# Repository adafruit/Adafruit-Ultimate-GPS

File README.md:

## Adafruit Ultimate GPS PCB

<a href="http://www.adafruit.com/products/4279"><br/>
Click here to purchase one from the Adafruit shop</a>
Other versions:
* <a href="https://www.adafruit.com/product/746">Adafruit Ultimate GPS Breakout</a>
* <a href="https://www.adafruit.com/product/3133">Adafruit Ultimate GPS FeatherWing</a>
* <a href="https://www.adafruit.com/product/1272">Adafruit Ultimate GPS Logger Shield</a>
* <a href="https://www.adafruit.com/product/2324">Adafruit Ultimate GPS HAT for Raspberry Pi</a>
* <a href="https://www.adafruit.com/product/1059">Flora Wearable Ultimate GPS Module</a>

PCB files for the Adafruit Ultimate GPS. 

Format is EagleCAD schematic and board layout
* https://www.adafruit.com/product/4279
* https://www.adafruit.com/product/746
* https://www.adafruit.com/product/3133
* https://www.adafruit.com/product/1272
* https://www.adafruit.com/product/2324
* https://www.adafruit.com/product/1059

### Description

These boards are built around the MTK3339 chipset, a no-nonsense, high-quality GPS module that can track up to 22 satellites on 66 channels, has an excellent high-sensitivity receiver (-165 dBm tracking!), and a built-in antenna. It can do up to 10 location updates a second for high speed, high sensitivity logging, or tracking. Power usage is incredibly low, only 20 mA during navigation.

We believe this is the Ultimate GPS module, so we named it that. It's got everything you want and more:

* -165 dBm sensitivity, 10 Hz updates, 66 channels
* 5V friendly design and only 20mA current draw
* RTC battery-compatible
* Built-in datalogging
* PPS output on fix
* Internal patch antenna + u.FL connector for external active antenna
* Fix status LED
* Pulse-Per-Second output

### License

Adafruit invests time and resources providing this open source design, please support Adafruit and open-source hardware by purchasing products from [Adafruit](https://www.adafruit.com)!

Designed by Limor Fried/Ladyada for Adafruit Industries.

Creative Commons Attribution/Share-Alike, all text above must be included in any redistribution. 
See license.txt for additional details.

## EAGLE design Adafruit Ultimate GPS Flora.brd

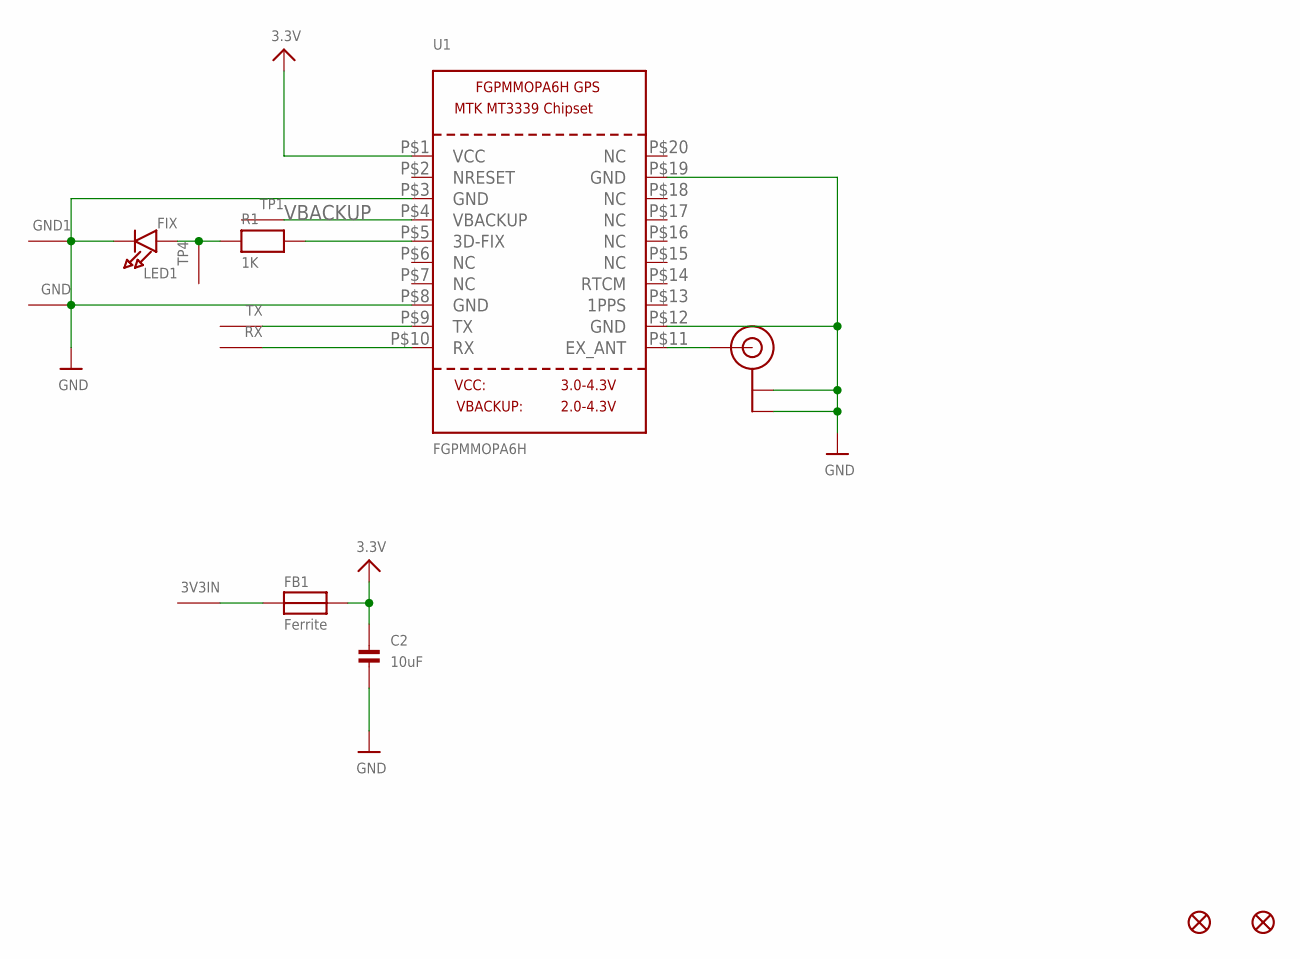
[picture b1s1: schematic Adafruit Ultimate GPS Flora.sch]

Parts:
3V3IN: SEWTAP-2.0IN; SEWINGTAP_2.0
C2: 10uF; 0805
FB1: Ferrite; 0805
FID1, FID2: FIDUCIAL""; FIDUCIAL_1MM
GND, GND1: SEWTAP-2.0IN; SEWINGTAP_2.0
LED1: FIX; CHIPLED_0805
R1: 1K; 0805
RX: SEWTAP-2.0IN; SEWINGTAP_2.0
TP1, TP4: SEWTAP-2.0IN; SEWINGTAP_2.0
TX: SEWTAP-2.0IN; SEWINGTAP_2.0
U1: FGPMMOPA6H
U$20: U.FL

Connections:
3.3V: C2.1, FB1.2, U1.P$1 (VCC)
GND: C2.2, GND.P$1, GND1.P$1, LED1.C, U1.P$3 (GND), U1.P$8 (GND), U1.P$12 (GND), U1.P$19 (GND), U$20.P$1 (GND), U$20.P$2 (GND)
unnamed: LED1.A, R1.1, TP4.P$1
unnamed: R1.2, U1.P$5 (3D-FIX)
unnamed: 3V3IN.P$1, FB1.1
unnamed: U1.P$11 (EX_ANT), U$20.P$3 (SIGNAL)
RX: RX.P$1, U1.P$10 (RX)
TX: TX.P$1, U1.P$9 (TX)
VBACKUP: TP1.P$1, U1.P$4 (VBACKUP)

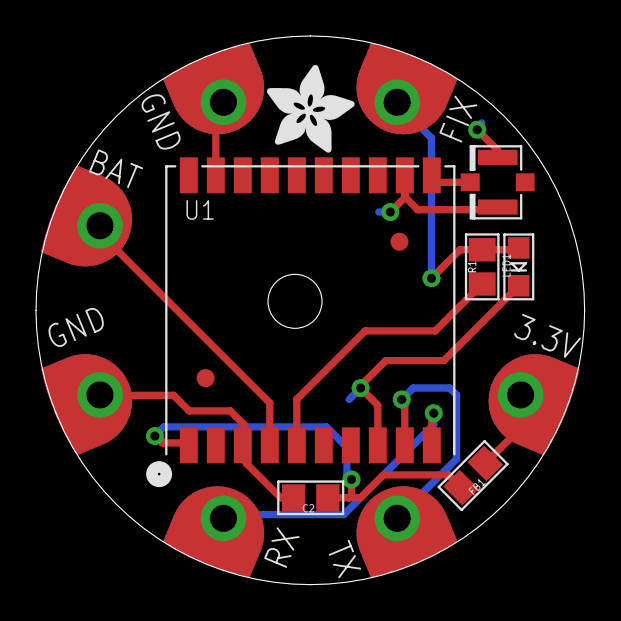
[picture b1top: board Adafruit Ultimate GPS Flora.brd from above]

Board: 2 copper layers, 30.5 x 30.5 mm, 17 parts (1 on the bottom side), 9 nets.

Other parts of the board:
U$6: ADAFRUIT_5MM
U$7: FLORASMALL

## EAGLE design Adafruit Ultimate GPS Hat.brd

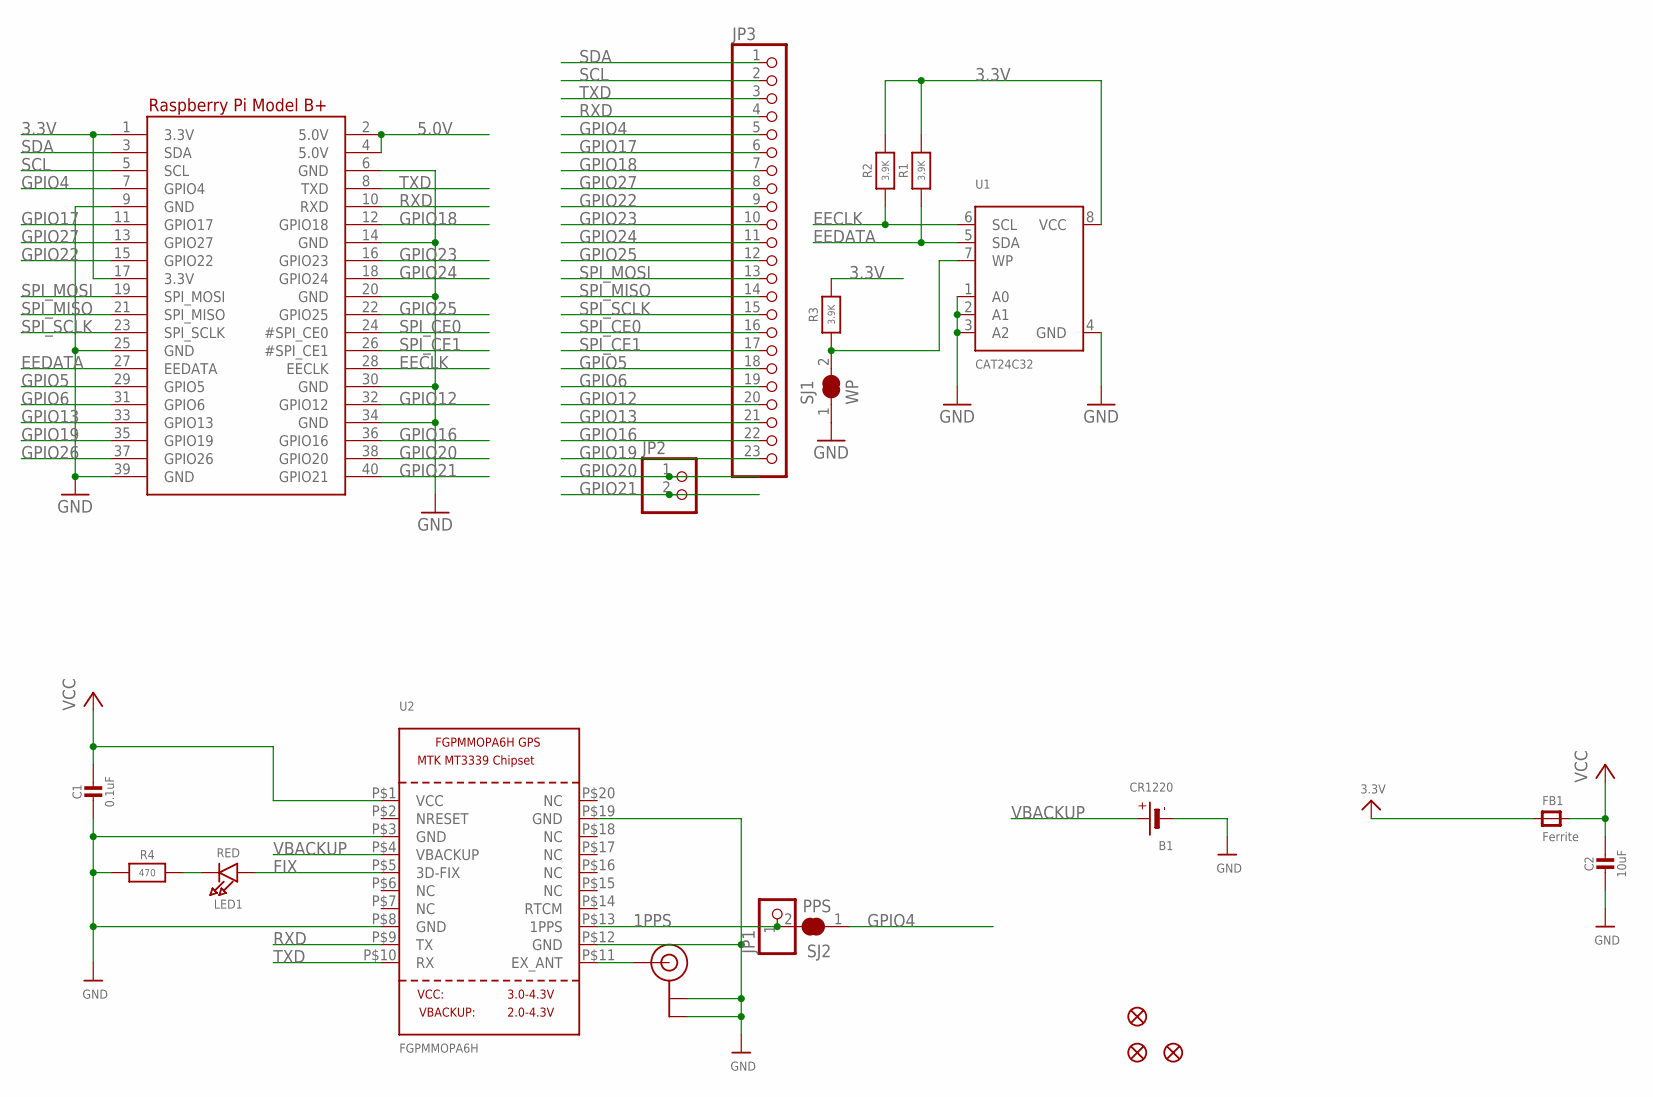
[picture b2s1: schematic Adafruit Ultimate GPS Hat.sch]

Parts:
B1: CR1220
C1: 0.1uF; 0805-NO
C2: 10uF; 0805-NO
FB1: Ferrite; 0805
FID1, FID2, FID3: FIDUCIAL_1MM
JP1: PINHD-1X1CB; 1X01-CLEANBIG
JP2: HEADER-1X2ROUND; 1X02_ROUND
JP3: HEADER-1X23; 1X23_ROUND_70MIL
LED1: RED; CHIPLED_0805
R1, R2, R3: 3.9K; 0805-NO
R4: 470; 0805-NO
RPI1: RASPBERRYPI_BPLUS_HATSLOTS; PI_HAT_SLOTS
SJ1: WP; SOLDERJUMPER_CLOSEDWIRE
SJ2: PPS; SOLDERJUMPER_CLOSEDWIRE
U1: CAT24C32; SOIC8_150MIL
U2: FGPMMOPA6H
U$20: U.FL

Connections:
1PPS: JP1.1, SJ2.2, U2.P$13 (1PPS)
3.3V: FB1.1, R1.2, R2.2, R3.2, RPI1.1 (3.3V), RPI1.17 (3.3V), U1.8 (VCC)
5.0V: RPI1.2 (5.0V), RPI1.4 (5.0V)
EECLK: R2.1, RPI1.28 (EECLK), U1.6 (SCL)
EEDATA: R1.1, RPI1.27 (EEDATA), U1.5 (SDA)
FIX: LED1.A, U2.P$5 (3D-FIX)
GND: B1.-, C1.2, C2.2, R4.1, RPI1.6 (GND), RPI1.9 (GND), RPI1.14 (GND), RPI1.20 (GND), RPI1.25 (GND), RPI1.30 (GND), RPI1.34 (GND), RPI1.39 (GND), SJ1.1, U1.1 (A0), U1.2 (A1), U1.3 (A2), U1.4 (GND), U2.P$3 (GND), U2.P$8 (GND), U2.P$12 (GND), U2.P$19 (GND), U$20.P$1 (GND), U$20.P$2 (GND)
GPIO4: JP3.5, RPI1.7 (GPIO4), SJ2.1
GPIO5: JP3.18, RPI1.29 (GPIO5)
GPIO6: JP3.19, RPI1.31 (GPIO6)
GPIO12: JP3.20, RPI1.32 (GPIO12)
GPIO13: JP3.21, RPI1.33 (GPIO13)
GPIO16: JP3.22, RPI1.36 (GPIO16)
GPIO17: JP3.6, RPI1.11 (GPIO17)
GPIO18: JP3.7, RPI1.12 (GPIO18)
GPIO19: JP3.23, RPI1.35 (GPIO19)
GPIO20: JP2.1, RPI1.38 (GPIO20)
GPIO21: JP2.2, RPI1.40 (GPIO21)
GPIO22: JP3.9, RPI1.15 (GPIO22)
GPIO23: JP3.10, RPI1.16 (GPIO23)
GPIO24: JP3.11, RPI1.18 (GPIO24)
GPIO25: JP3.12, RPI1.22 (GPIO25)
GPIO26: RPI1.37 (GPIO26)
GPIO27: JP3.8, RPI1.13 (GPIO27)
unnamed: R3.1, SJ1.2, U1.7 (WP)
unnamed: LED1.C, R4.2
unnamed: U2.P$11 (EX_ANT), U$20.P$3 (SIGNAL)
RXD: JP3.4, RPI1.10 (RXD), U2.P$9 (TX)
SCL: JP3.2, RPI1.5 (SCL)
SDA: JP3.1, RPI1.3 (SDA)
SPI_CE0: JP3.16, RPI1.24 (#SPI_CE0)
SPI_CE1: JP3.17, RPI1.26 (#SPI_CE1)
SPI_MISO: JP3.14, RPI1.21 (SPI_MISO)
SPI_MOSI: JP3.13, RPI1.19 (SPI_MOSI)
SPI_SCLK: JP3.15, RPI1.23 (SPI_SCLK)
TXD: JP3.3, RPI1.8 (TXD), U2.P$10 (RX)
VBACKUP: B1.+$1 (+), B1.+$2 (+), U2.P$4 (VBACKUP)
VCC: C1.1, C2.1, FB1.2, U2.P$1 (VCC)

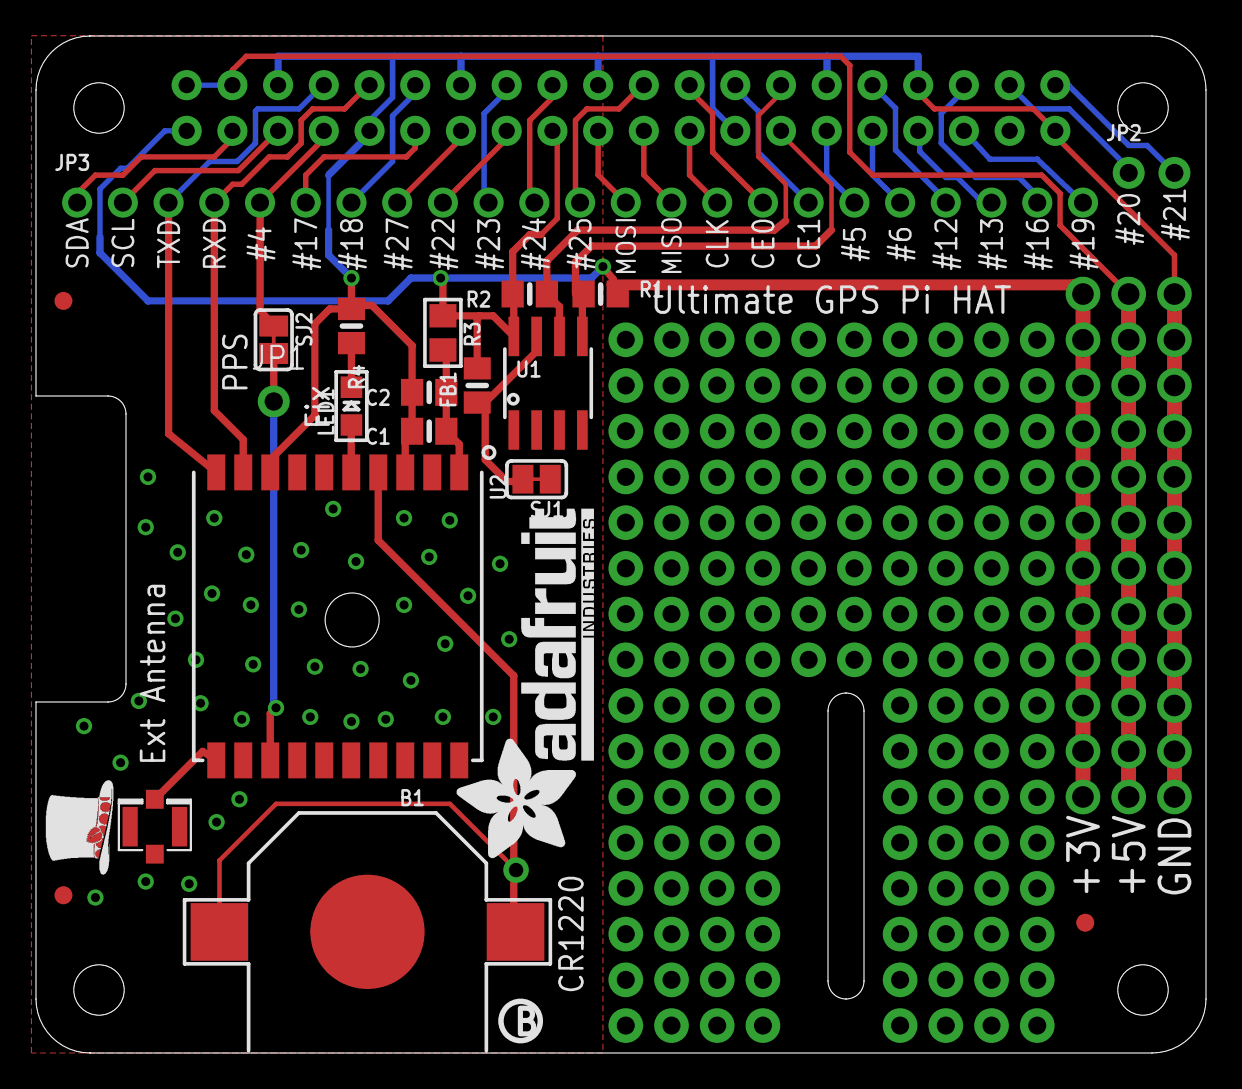
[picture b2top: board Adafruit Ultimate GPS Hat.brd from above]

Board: 2 copper layers, 65.0 x 56.5 mm, 24 parts (0 on the bottom side), 37 nets.

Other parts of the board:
U$3: ADAFRUIT_TEXT_20MM
U$4: PIHATLOGO
U$6: PCBFEAT-REV-056

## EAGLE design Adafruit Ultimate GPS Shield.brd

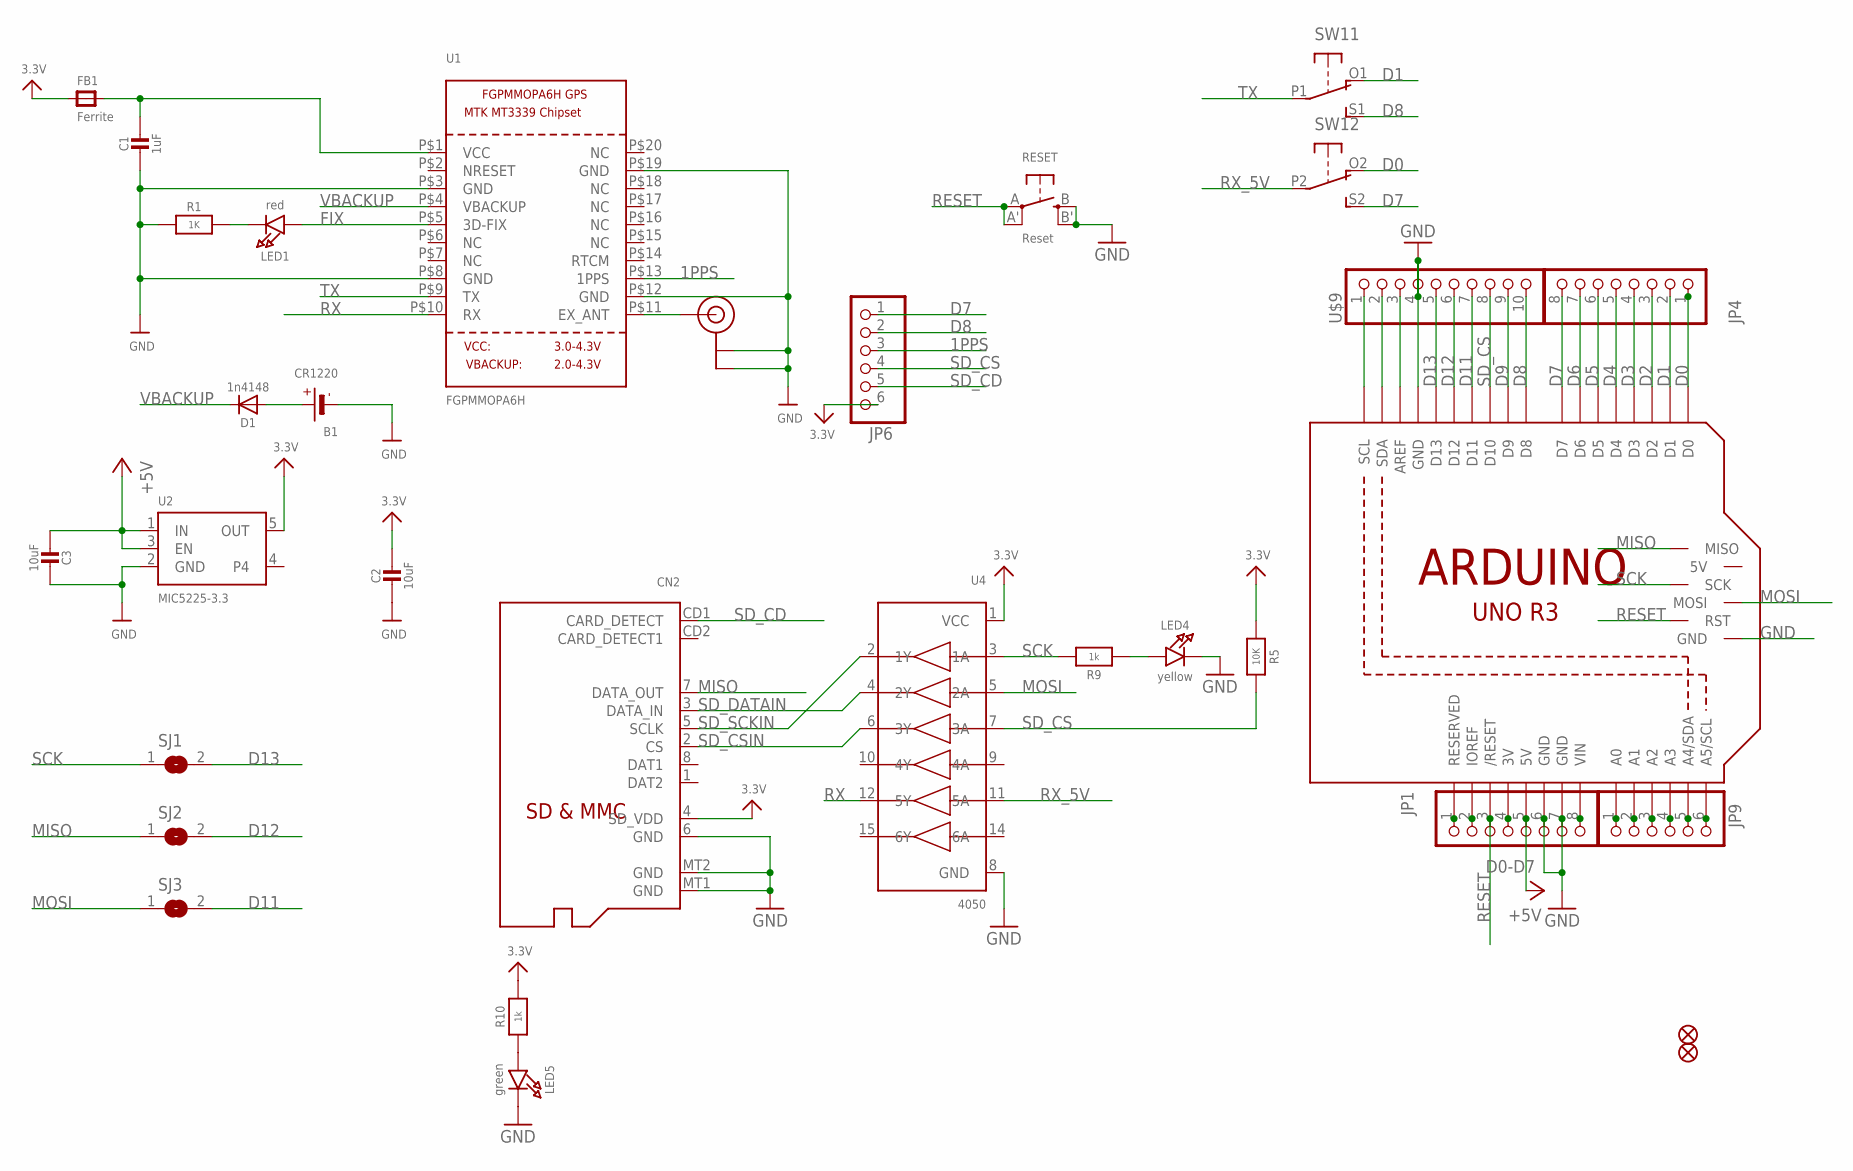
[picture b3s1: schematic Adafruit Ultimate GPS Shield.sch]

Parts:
B1: CR1220
C1: 1uF; 0805-NO
C2, C3: 10uF; 0805-NO
CN2: MICROSD
D1: 1n4148; SOD-323
FB1: Ferrite; 0805
FID1, FID2: FIDUCIAL""; FIDUCIAL_1MM
JP1: D0-D7; 1X08-BIG
JP4: PINHD-1X8BIG; 1X08-BIG
JP6, JP9: PINHD-1X6B; 1X06-BIG
LED1: red; CHIPLED_0805_NOOUTLINE
LED4: yellow; CHIPLED_0805_NOOUTLINE
LED5: green; CHIPLED_0805_NOOUTLINE
M1: ARDUINO_R3_ICSP_NODIM; ARDUINOR3_ICSP_NODIM
R1: 1K; 0805-NO
R5: 10K; 0805-NO
R9, R10: 1k; 0805-NO
RESET: Reset; EVQ-Q2
SJ1, SJ2, SJ3: SOLDERJUMPER; SOLDERJUMPER_ARROW_NOPASTE
SW1: DPDT-EG1390; EG1390
U1: FGPMMOPA6H
U2: MIC5225-3.3; SOT23-5
U4: 4050; SOIC16
U$9: PINHD-1X10; 1X10-BIG
U$20: U.FL

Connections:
1PPS: JP6.3, U1.P$13 (1PPS)
3.3V: C2.1, CN2.4 (SD_VDD), FB1.1, JP6.6, R5.1, R10.2, U2.5 (OUT), U4.1 (VCC)
3V: JP1.4, M1.3V
+5V: C3.1, JP1.5, M1.5V, U2.1 (IN), U2.3 (EN)
A0: JP9.1, M1.A0
A1: JP9.2, M1.A1
A2: JP9.3, M1.A2
A3: JP9.4, M1.A3
A4: JP9.5, M1.A4 (A4/SDA)
A5: JP9.6, M1.A5 (A5/SCL)
AREF: M1.AREF, U$9.3
D0: JP4.1, M1.D0, SW1.O2 (O)
D1: JP4.2, M1.D1, SW1.O1 (O)
D2: JP4.3, M1.D2
D3: JP4.4, M1.D3
D4: JP4.5, M1.D4
D5: JP4.6, M1.D5
D6: JP4.7, M1.D6
D7: JP4.8, JP6.1, M1.D7, SW1.S2 (S)
D8: JP6.2, M1.D8, SW1.S1 (S), U$9.10
D9: M1.D9, U$9.9
D11: M1.D11, SJ3.2, U$9.7
D12: M1.D12, SJ2.2, U$9.6
D13: M1.D13, SJ1.2, U$9.5
FIX: LED1.A, U1.P$5 (3D-FIX)
GND: B1.-, C1.2, C2.2, C3.2, CN2.6 (GND), CN2.MT1 (GND), CN2.MT2 (GND), JP1.6, JP1.7, LED4.C, LED5.C, M1.GND, M1.GND@1 (GND), M1.GND@2 (GND), M1.GND@3 (GND), R1.1, RESET.B (S), RESET.B' (S1), U1.P$3 (GND), U1.P$8 (GND), U1.P$12 (GND), U1.P$19 (GND), U2.2 (GND), U4.8 (GND), U$9.4, U$20.P$1 (GND), U$20.P$2 (GND)
IOREF: JP1.2, M1.IOREF
MISO: CN2.7 (DATA_OUT), M1.MISO, SJ2.1
MOSI: M1.MOSI, SJ3.1, U4.5 (2A)
unnamed: C1.1, FB1.2, U1.P$1 (VCC)
unnamed: LED1.C, R1.2
unnamed: B1.+$1 (+), B1.+$2 (+), D1.A
unnamed: U1.P$11 (EX_ANT), U$20.P$3 (SIGNAL)
unnamed: LED4.A, R9.1
unnamed: LED5.A, R10.1
NC: JP1.1, M1.RESERVED
RESET: JP1.3, M1.RESET (/RESET), M1.RESET_ICSP (RST), RESET.A, RESET.A' (P1)
RX: U1.P$10 (RX), U4.12 (5Y)
RX_5V: SW1.P2, U4.11 (5A)
SCK: M1.SCK, R9.2, SJ1.1, U4.3 (1A)
SCL: M1.SCL, U$9.1
SDA: M1.SDA, U$9.2
SD_CD: CN2.CD1 (CARD_DETECT), JP6.5
SD_CS: JP6.4, M1.D10, R5.2, U4.7 (3A), U$9.8
SD_CSIN: CN2.2 (CS), U4.6 (3Y)
SD_DATAIN: CN2.3 (DATA_IN), U4.4 (2Y)
SD_SCKIN: CN2.5 (SCLK), U4.2 (1Y)
TX: SW1.P1, U1.P$9 (TX)
VBACKUP: D1.C, U1.P$4 (VBACKUP)
VIN: JP1.8, M1.VIN

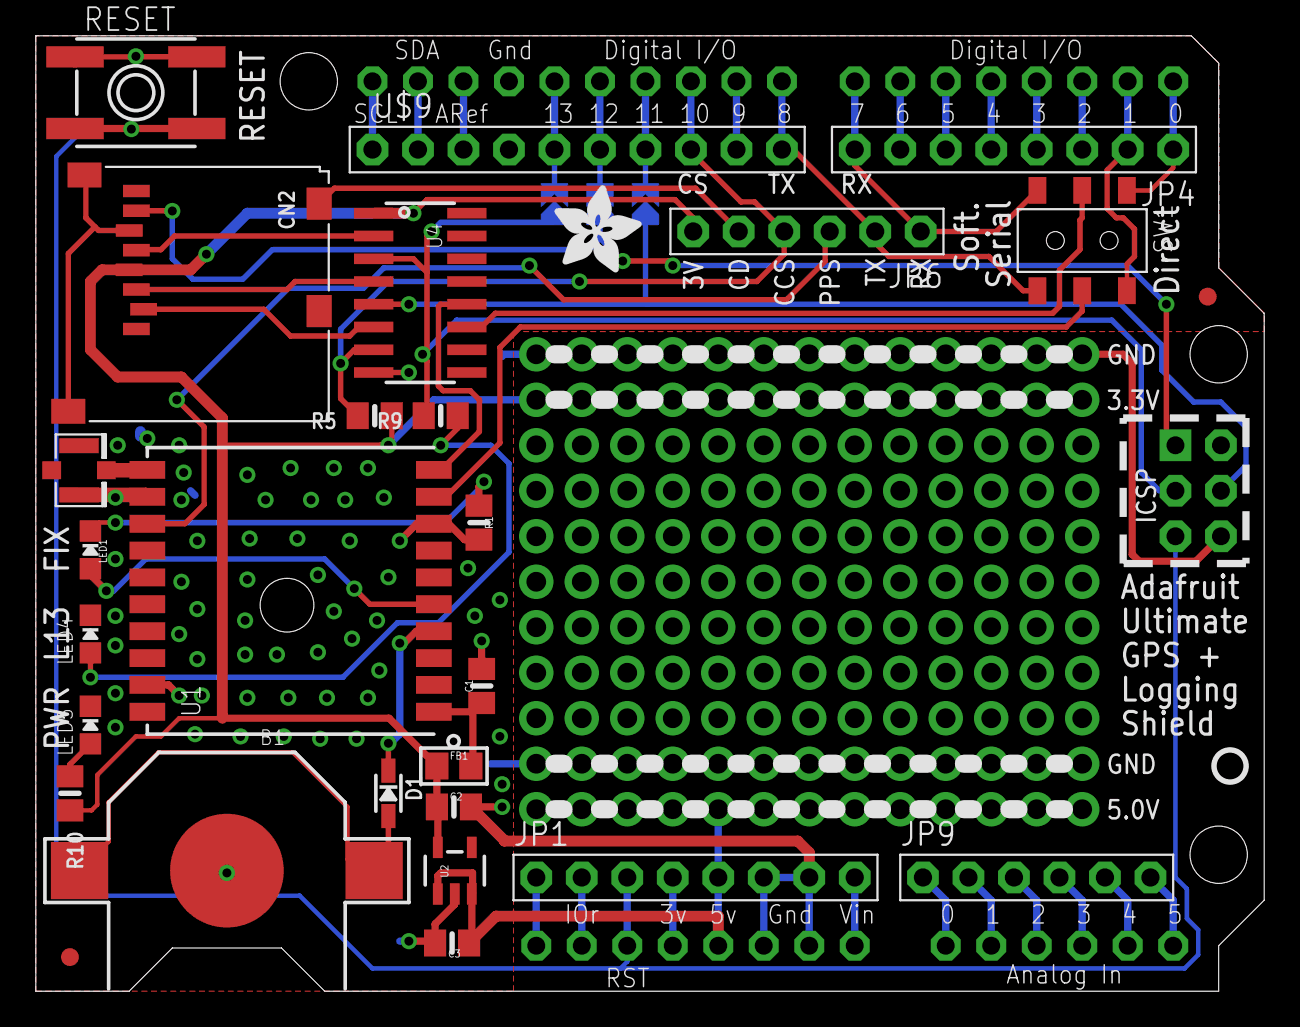
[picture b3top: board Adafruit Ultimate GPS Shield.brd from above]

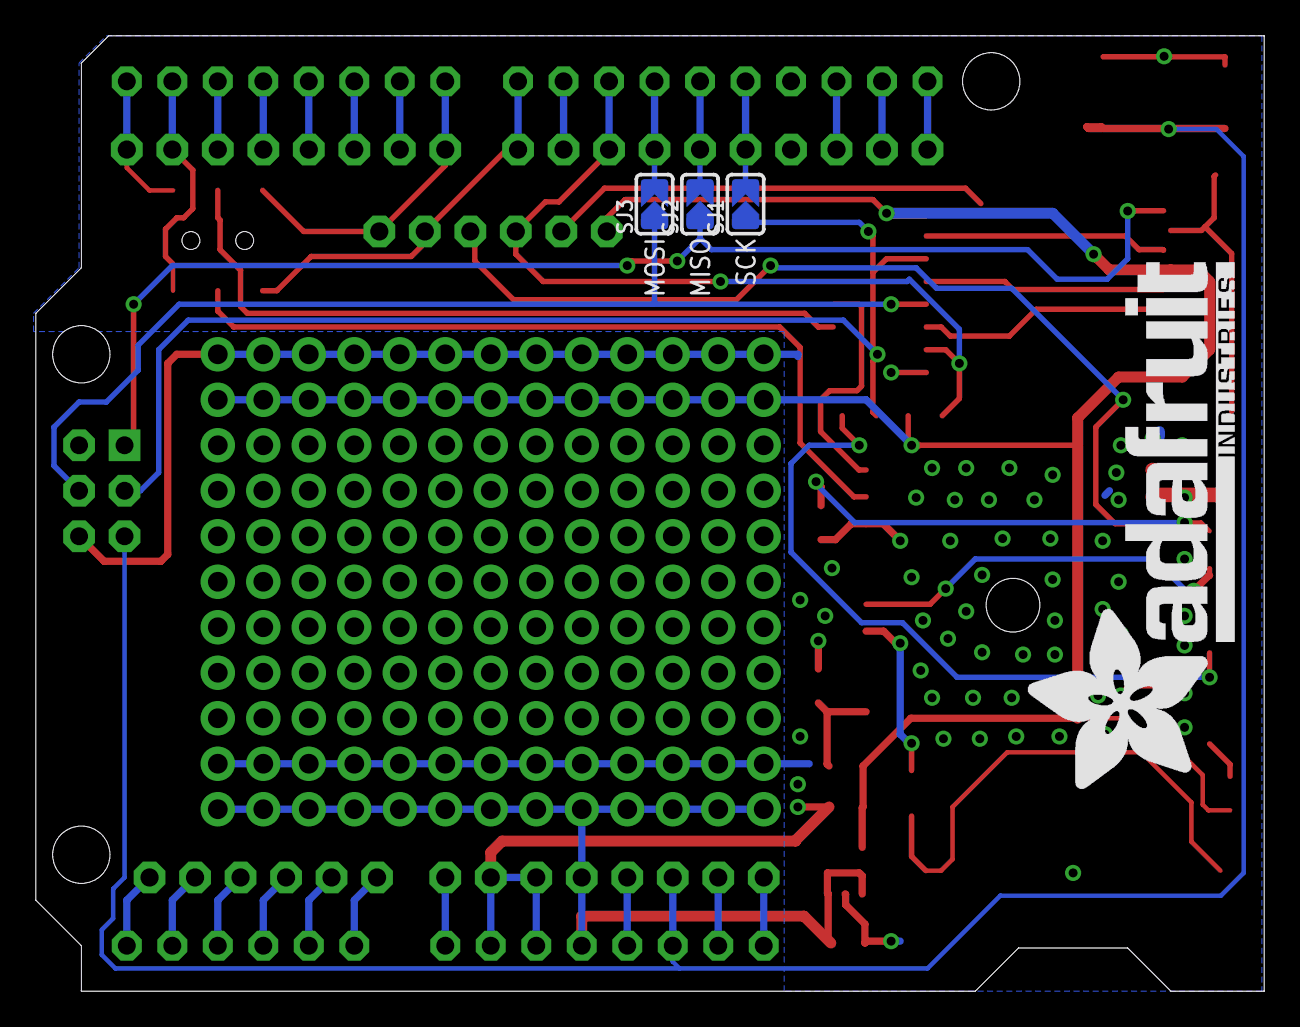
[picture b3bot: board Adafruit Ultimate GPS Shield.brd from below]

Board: 2 copper layers, 68.6 x 53.3 mm, 34 parts (4 on the bottom side), 50 nets.

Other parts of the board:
U$13: ADAFRUIT_5MM
U$15: ADAFRUIT_TEXT_30MM
U$16: PCBFEAT-REV-040

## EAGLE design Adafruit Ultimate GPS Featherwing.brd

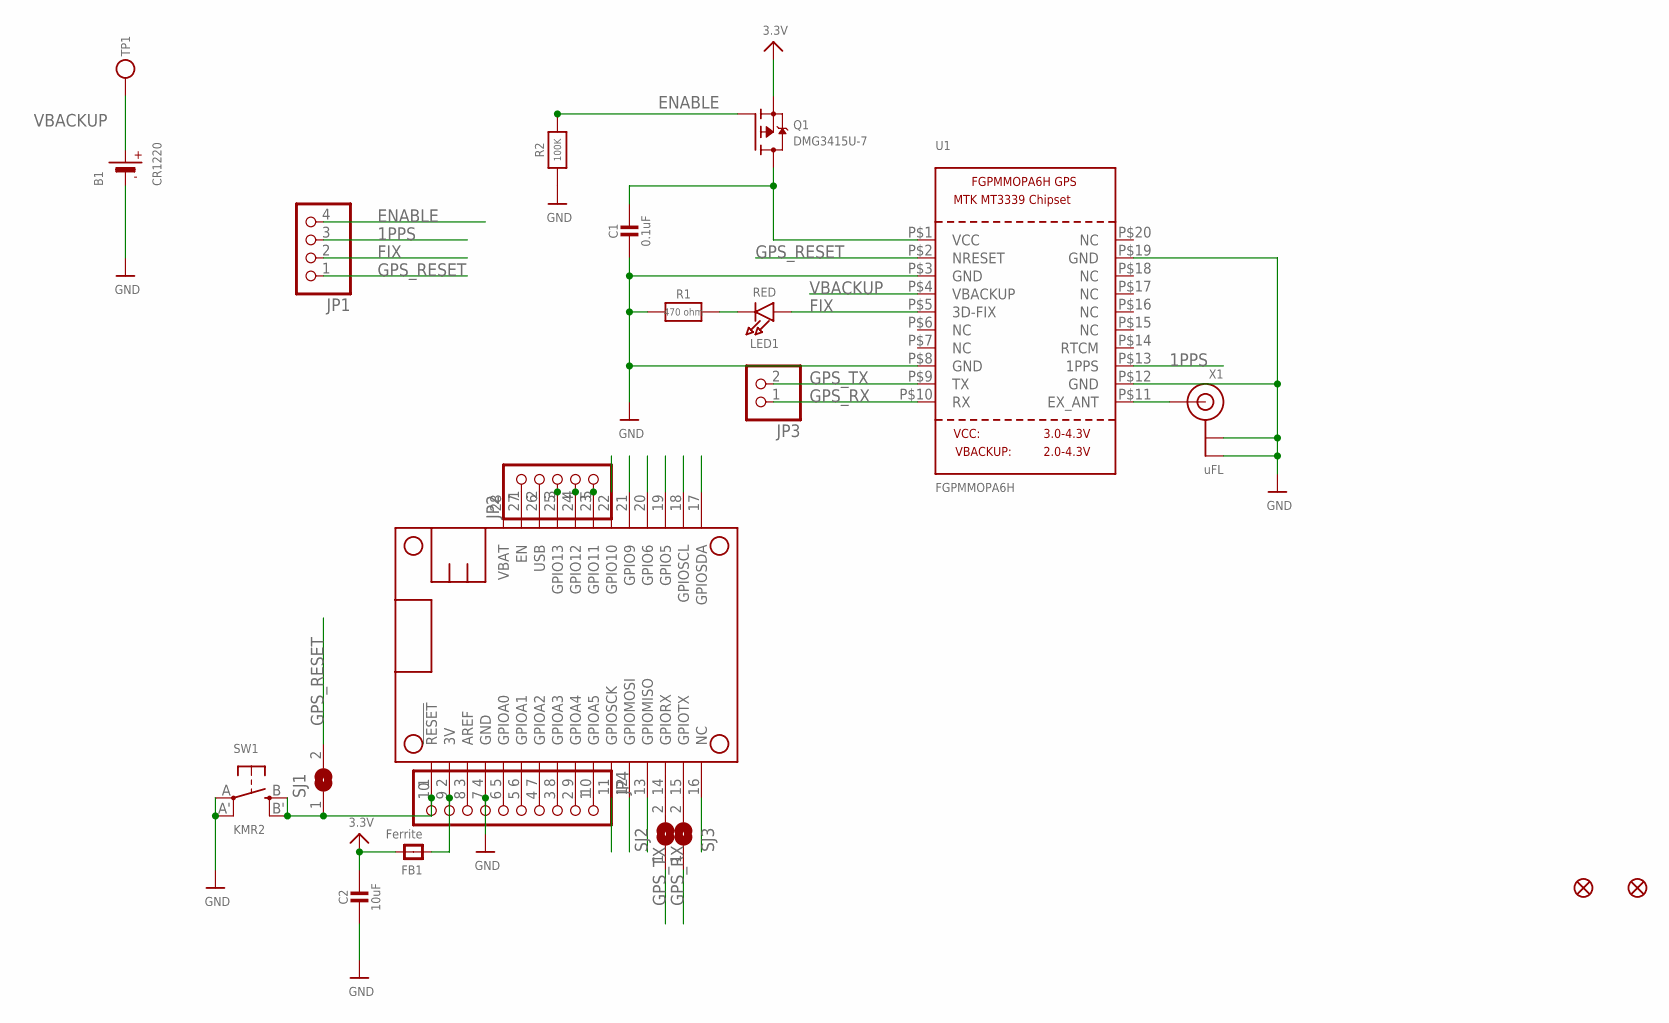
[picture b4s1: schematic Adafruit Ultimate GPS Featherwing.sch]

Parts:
B1: CR1220; CR1220-2
C1: 0.1uF; 0805-NO
C2: 10uF; 0805-NO
FB1: Ferrite; 0805-NO
FID1, FID2: FIDUCIAL""; FIDUCIAL_1MM
JP1: HEADER-1X4ROUND; 1X04_ROUND
JP2: HEADER-1X570MIL; 1X05_ROUND_70
JP3: HEADER-1X2ROUND; 1X02_ROUND
JP4: HEADER-1X10ROUND; 1X10_ROUND
LED1: RED; CHIPLED_0805_NOOUTLINE
MS1: FEATHERWING
Q1: DMG3415U-7; SOT23-WIDE
R1: 470 ohm; 0805-NO
R2: 100K; 0805-NO
SJ1: SOLDERJUMPER; SOLDERJUMPER_ARROW_NOPASTE
SJ2, SJ3: SOLDERJUMPERCLOSED; SOLDERJUMPER_CLOSEDWIRE
SW1: KMR2; BTN_KMR2_4.6X2.8
TP1: TESTPOINTROUND1.5MM; TESTPOINT_ROUND_1.5MM
U1: FGPMMOPA6H
X1: uFL; U.FL

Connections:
1PPS: JP1.3, U1.P$13 (1PPS)
3.3V: C2.1, FB1.2, Q1.2 (S)
3V: FB1.1, JP4.9, MS1.2 (3V)
A: JP4.6, MS1.5 (GPIOA0)
AREF: JP4.8, MS1.3 (AREF)
B: JP4.5, MS1.6 (GPIOA1)
C: JP4.4, MS1.7 (GPIOA2)
D: JP4.3, MS1.8 (GPIOA3)
E: JP4.2, MS1.9 (GPIOA4)
EN: JP2.1, MS1.27 (EN)
ENABLE: JP1.4, Q1.1 (G), R2.2
F: JP4.1, MS1.10 (GPIOA5)
FIX: JP1.2, LED1.A, U1.P$5 (3D-FIX)
G: MS1.16 (NC)
GND: B1.-, C1.2, C2.2, JP4.7, MS1.4 (GND), R1.1, R2.1, SW1.A, SW1.A' (P1), U1.P$3 (GND), U1.P$8 (GND), U1.P$12 (GND), U1.P$19 (GND), X1.1 (GND), X1.2 (GND)
GPS_RESET: JP1.1, SJ1.2, U1.P$2 (NRESET)
GPS_RX: JP3.1, SJ3.1, U1.P$10 (RX)
GPS_TX: JP3.2, SJ2.1, U1.P$9 (TX)
H: MS1.19 (GPIO5)
I: MS1.20 (GPIO6)
J: MS1.21 (GPIO9)
K: MS1.22 (GPIO10)
L: JP2.5, MS1.23 (GPIO11)
M: JP2.4, MS1.24 (GPIO12)
MISO: MS1.13 (GPIOMISO)
MOSI: MS1.12 (GPIOMOSI)
N: JP2.3, MS1.25 (GPIO13)
unnamed: LED1.C, R1.2
unnamed: U1.P$11 (EX_ANT), X1.3 (SIGNAL)
unnamed: C1.1, Q1.3 (D), U1.P$1 (VCC)
RST: JP4.10, MS1.1 (!RESET), SJ1.1, SW1.B (S), SW1.B' (S1)
RX: MS1.14 (GPIORX), SJ2.2
SCK: MS1.11 (GPIOSCK)
SCL: MS1.18 (GPIOSCL)
SDA: MS1.17 (GPIOSDA)
TX: MS1.15 (GPIOTX), SJ3.2
USB: JP2.2, MS1.26 (USB)
VBACKUP: B1.+, TP1.P$1, U1.P$4 (VBACKUP)

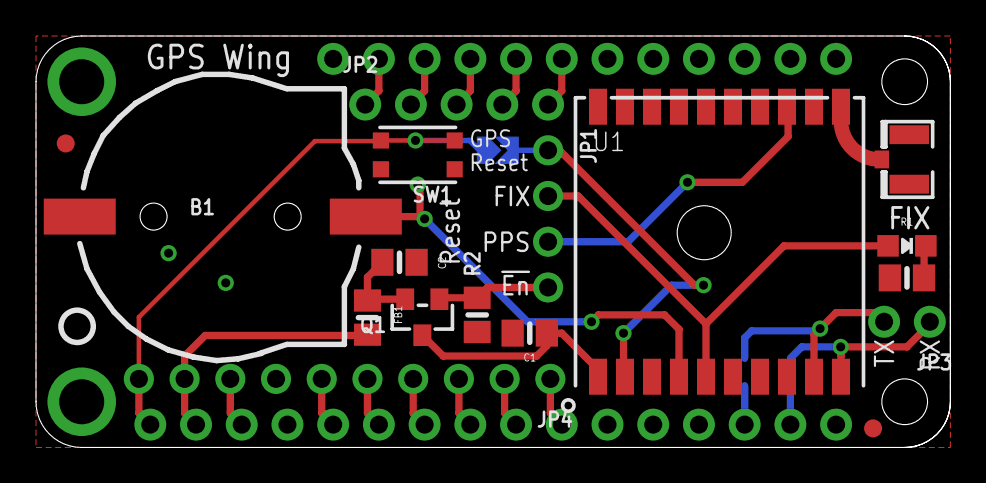
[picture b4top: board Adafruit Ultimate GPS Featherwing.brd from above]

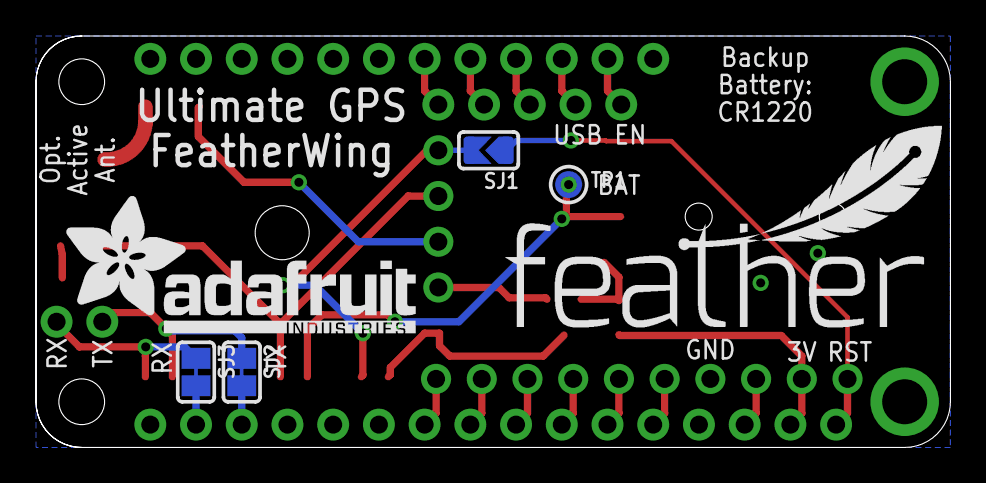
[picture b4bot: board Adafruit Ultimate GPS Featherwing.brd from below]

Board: 2 copper layers, 50.8 x 22.9 mm, 25 parts (6 on the bottom side), 28 nets.

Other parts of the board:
U$9: PCBFEAT-REV-040
U$10: FEATHERLOGO
U$11: ADAFRUIT_TEXT_20MM

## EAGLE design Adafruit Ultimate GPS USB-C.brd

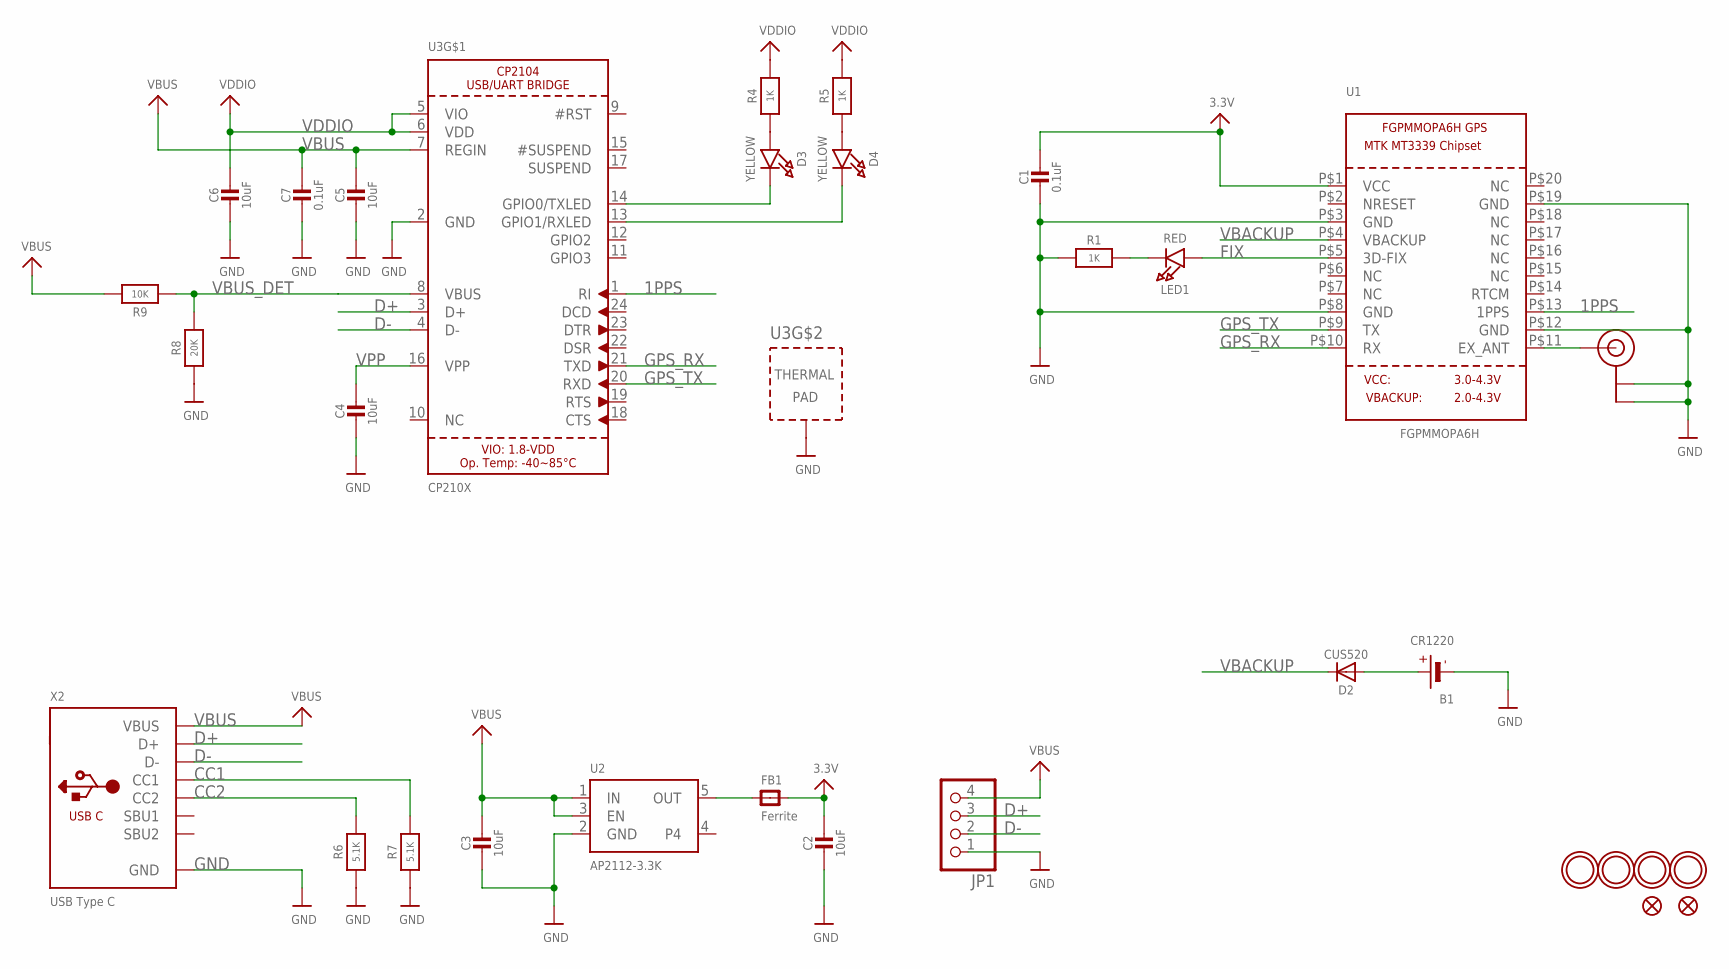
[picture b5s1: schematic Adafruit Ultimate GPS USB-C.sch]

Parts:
B1: CR1220
C1, C7: 0.1uF; 0603-NO
C2, C3, C4, C5, C6: 10uF; 0805-NO
D2: CUS520; SOD-323
D3, D4: YELLOW; CHIPLED_0805_NOOUTLINE
FB1: Ferrite; 0805-NO
FID1, FID2: FIDUCIAL_1MM
JP1: HEADER-1X4ROUND; 1X04_ROUND
LED1: RED; CHIPLED_0805_NOOUTLINE
R1, R4, R5: 1K; 0603-NO
R6, R7: 5.1K; 0603-NO
R8: 20K; 0603-NO
R9: 10K; 0603-NO
U1: FGPMMOPA6H
U2: AP2112-3.3K; SOT23-5
U3: CP210X; QFN24_4MM_SMSC
U$8, U$9, U$35, U$36: MOUNTINGHOLE2.5; MOUNTINGHOLE_2.5_PLATED
U$20: U.FL
X2: USB Type C; USB_C_CUSB31-CFM2AX-01-X

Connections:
1PPS: U1.P$13 (1PPS), U3.1 (RI)
3.3V: C1.1, C2.1, FB1.2, U1.P$1 (VCC)
CC1: R7.2, X2.A5 (CC1)
CC2: R6.2, X2.B5 (CC2)
D+: JP1.3, U3.3 (D+), X2.A6 (D+), X2.B6 (D+)
D-: JP1.2, U3.4 (D-), X2.A7 (D-), X2.B7 (D-)
FIX: LED1.A, U1.P$5 (3D-FIX)
GND: B1.-, C1.2, C2.2, C3.2, C4.2, C5.2, C6.2, C7.2, JP1.1, R1.1, R6.1, R7.1, R8.1, U1.P$3 (GND), U1.P$8 (GND), U1.P$12 (GND), U1.P$19 (GND), U2.2 (GND), U3.2 (GND), U3.THERM (TP), U$20.P$1 (GND), U$20.P$2 (GND), X2.A1B12 (GND), X2.B1A12 (GND)
GPS_RX: U1.P$10 (RX), U3.21 (TXD)
GPS_TX: U1.P$9 (TX), U3.20 (RXD)
unnamed: B1.+$1 (+), B1.+$2 (+), D2.A
unnamed: LED1.C, R1.2
unnamed: FB1.1, U2.5 (OUT)
unnamed: U1.P$11 (EX_ANT), U$20.P$3 (SIGNAL)
unnamed: D3.A, R4.1
unnamed: D4.A, R5.1
unnamed: D3.C, U3.14 (GPIO0/TXLED)
unnamed: D4.C, U3.13 (GPIO1/RXLED)
VBACKUP: D2.C, U1.P$4 (VBACKUP)
VBUS: C3.1, C5.1, C7.1, JP1.4, R9.2, U2.1 (IN), U2.3 (EN), U3.7 (REGIN), X2.A4B9 (VBUS), X2.B4A9 (VBUS)
VBUS_DET: R8.2, R9.1, U3.8 (VBUS)
VDDIO: C6.1, R4.2, R5.2, U3.5 (VIO), U3.6 (VDD)
VPP: C4.1, U3.16 (VPP)

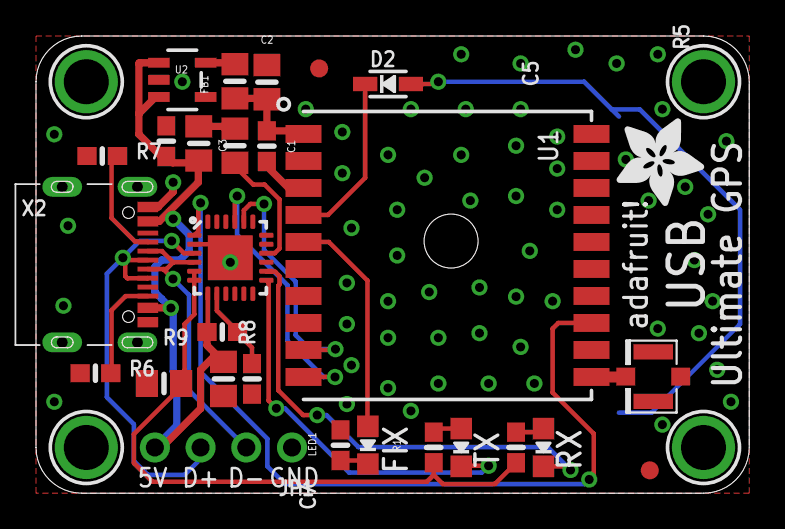
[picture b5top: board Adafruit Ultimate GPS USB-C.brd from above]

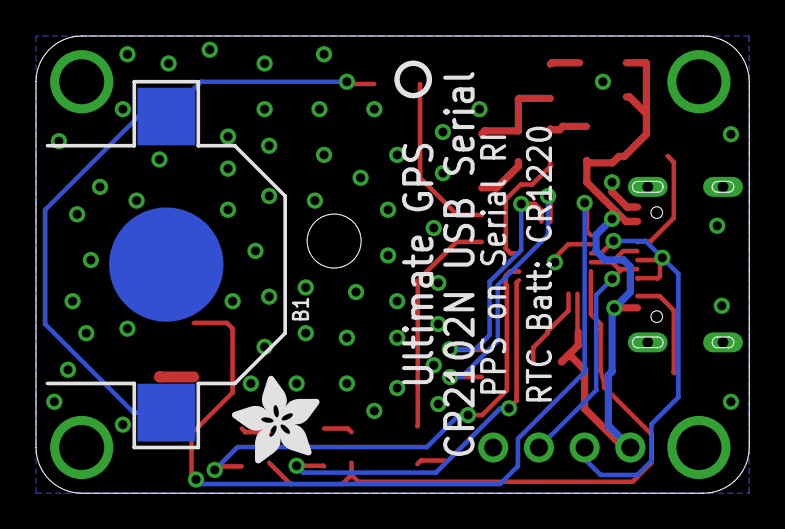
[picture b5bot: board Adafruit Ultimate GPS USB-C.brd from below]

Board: 2 copper layers, 39.6 x 25.4 mm, 35 parts (3 on the bottom side), 23 nets.

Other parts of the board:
U$13, U$18: ADAFRUIT_5MM
U$16: PCBFEAT-REV-040

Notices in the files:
parts and their libraries:
microbuilder: This work is placed in the public domain, and may be freely used for commercial and non-commercial work with the following conditions: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
